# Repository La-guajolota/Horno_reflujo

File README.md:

<!-- @format -->

# 🔥 Homemade SMD Reflow Oven 🔥

## 📑 Table of Contents

- [Overview](#-overview)
- [Project Demo](#-project-demo)
- [Workflow](#-workflow)
- [Technical Challenges](#-technical-challenges)
- [Repository Structure](#-repository-structure)
- [Requirements & Dependencies](#-requirements--dependencies)
- [Installation & Usage](#-installation--usage)
- [To-Do List](#-to-do-list)
- [Possible Improvements](#-possible-improvements)
- [Safety Considerations](#-safety-considerations)
- [Contributing](#-contributing)
- [Reference Links](#-reference-links)
- [License](#-license)

---

## 📝 Overview

The **SMD Reflow Oven** is an open-source project designed for precise SMD soldering. It utilizes configurable thermal profiles managed by an **STM32F411** microcontroller and a web-based GUI hosted on an **ESP01-S**. Key features include real-time PID temperature control, smart power management, and robust safety systems.

> ✅ **Functional Demo**: All core features (PID control, temperature sensing, web GUI, and the reflow algorithm) are fully operational and ready for soldering SMD components.
> 🚧 **Active Development**: Both the firmware and hardware are under continuous improvement.

---

## 📹 Project Demo

See the oven in action! This video demonstrates its current functionality and soldering capabilities.

<p align="center">
<a href="https://youtu.be/XSk6v5LdElc?si=d4BS0npnXu5F3Sj0" target="_blank">
<b>Watch a video demonstration of the oven in action</b>
</a>
</p>

---

## 🔄 Workflow

<details>
<summary><b>Step-by-step SMD soldering process</b></summary>

### 1. 📋 PCB Preparation

- Apply solder paste evenly using a stencil.
- Carefully place the SMD components onto the pasted pads.

### 2. ⚙️ Oven Setup

- Power the oven (120V AC).
- Select the appropriate thermal profile for your solder type via the web GUI.
- Verify that all safety systems are active.

### 3. 🔥 Soldering Process

- Place the prepared PCB inside the oven chamber.
- Close the door securely and start the process from the interface.
- Monitor the temperature curve in real-time to ensure it follows the selected profile.

### 4. 🔍 Final Inspection

- Wait for the **Cooldown** phase to complete before opening the door.
- Allow the PCB to cool completely before handling.
- Inspect the solder joints with a magnifier or microscope for any defects.
- Perform electrical tests to check for shorts or open circuits.

<p align="center">
<a href="https://youtube.com/shorts/ztY0c23UdZQ?si=FxfqCBQ48sNtS6zn" target="_blank">
📺 Watch the final results on YouTube
</a>
</p>
</details>

---

## 🎯 Technical Challenges

| Challenge                 | Solution Approach                                                                                                           |
| :------------------------ | :-------------------------------------------------------------------------------------------------------------------------- |
| **Temperature Control**   | Ensure uniform heat distribution, implement adaptable thermal curves, and design profiles to prevent component microcracks. |
| **Risk Management**       | Implement automatic overheating detection and shutoff, along with a system for filtering potentially toxic vapors.          |
| **Operational Precision** | Calibrate sensors accurately and synchronize heating/cooling stages for reliable and repeatable results.                    |

---

## 📂 Repository Structure

The **Serial Peripheral Interface (SPI)** is crucial in this project for fast communication between the STM32 microcontroller and peripherals like the **MAX6675 thermocouple sensors**, ensuring precise, real-time temperature readings for the PID control loop.

```
.
├── Firmware/                   # Firmware for all microcontrollers
│   ├── esp01/                  # ESP-01S firmware and related tools
│   ├── nextionGUI/             # Nextion HMI screen GUI files
│   └── stm32f411/              # STM32F411 firmware and related tools
├── Hardware/                   # Hardware design files (schematics, PCB)
│   ├── horno_no_modificado/  # Original, unmodified oven schematics
│   └── horno_reflujo/        # Custom reflow oven hardware
├── pictures/                   # Project images and photos
├── .gitignore                  # Git ignore file
├── LICENSE                     # Project license
└── README.md                   # This README file
```

---

## 📦 Requirements & Dependencies

### Software

- **PlatformIO**: Recommended for firmware development.
- **Python 3.x**: For data analysis and utility scripts.
- **KiCad**: For viewing and editing hardware schematics and PCB layouts.
- **STM32CubeIDE**: Optional, for STM32-specific development.

### Hardware

- Refer to the **Bill of Materials (BOM)** located in the `Hardware/horno_reflujo/` directory for a complete list of components.

---

## 🛠️ Installation & Usage

1.  **Clone the Repository:**
    ```bash
    git clone https://github.com/La-guajolota/Horno_reflujo.git
    cd Horno_reflujo
    ```
2.  **Setup Firmware:**
    - Open the `Firmware/` and `stm32f411/` directories in PlatformIO.
    - Follow the specific setup instructions within each folder to compile and upload the firmware.
3.  **Assemble Hardware:**
    - Use the schematics and PCB files in the `Hardware/` directory as a guide.
    - Solder and assemble all components according to the BOM.
4.  **Calibrate & Test:**
    - Before the first use, perform temperature sensor calibration.
    - Test all safety systems to ensure they are functioning correctly.

---

## 📋 To-Do List

### High Priority

- [ ] Complete the documentation for hardware assembly.
- [ ] Implement a physical emergency stop button.
- [ ] Create a detailed guide for sensor calibration procedures.
- [ ] Add unit tests for critical firmware functions.

### Medium Priority

- [ ] Develop a mobile-friendly interface or a dedicated app.
- [ ] Add data logging and analysis features to track performance.
- [ ] Create 3D printable designs for the enclosure.

### Low Priority

- [ ] Integrate with PCB design software for profile suggestions.
- [ ] Add cloud connectivity for remote monitoring.

---

## 🚀 Possible Improvements

### Firmware Enhancements

- **Advanced PID Control**: Implement auto-tuning algorithms and adaptive control for even greater precision.
- **Enhanced Safety**: Add redundant sensors and fail-safe mechanisms.
- **Intuitive UI**: Improve the user interface with a touchscreen, OLED display, or rotary encoder.
- **IoT Integration**: Allow for remote monitoring and control over the internet.
- **Ventilation Control**: Develop an automated system to manage toxic vapor extraction.

### Hardware Upgrades

- **Improved Insulation**: Enhance thermal efficiency and user safety.
- **High-Accuracy Sensors**: Upgrade to more precise temperature sensors.
- **Modular Design**: Create a modular system to support different oven sizes.
- **Power Efficiency**: Optimize heating element control to reduce energy consumption.
- **Electrical Isolation**: Improve electrical isolation between high-voltage and low-voltage circuits.

---

## ⚠️ Safety Considerations

- ⚡ **High Voltage**: This project involves **120V AC**. Exercise extreme caution and ensure all connections are properly insulated.
- 🌡️ **High Temperatures**: The oven reaches temperatures capable of causing severe burns. Use protective equipment.
- 💨 **Ventilation**: Solder paste fumes can be toxic. Operate the oven in a well-ventilated area.
- 🔧 **Grounding**: Ensure the oven chassis is properly grounded to prevent electrical shock.
- 📏 **Calibration**: Regularly calibrate temperature sensors to maintain accuracy and prevent overheating.

---

## 🤝 Contributing

Contributions are welcome\! If you'd like to help improve this project, please follow these steps:

1.  **Fork the repository.**
2.  Create a new branch: `git checkout -b feature/your-amazing-feature`
3.  Make your changes and commit them: `git commit -m 'Add your amazing feature'`
4.  Push to your branch: `git push origin feature/your-amazing-feature`
5.  **Open a Pull Request** and describe the changes you've made.

Please report any bugs or suggest features by opening an issue on GitHub.

---

## 🔗 Reference Links

- [Nextion HMI Displays](https://nextion.tech/) – Official site for Nextion touchscreen displays.
- [gerber_to_scad (GitHub)](https://github.com/kirberich/gerber_to_scad) – Tool for generating 3D stencils from Gerber files.
- [SMD Soldering Guidelines](https://www.surfacemountprocess.com/reflow-soldering-process.html) – Comprehensive guide to the reflow soldering process.
- [Reflow Soldering Profiles (SMTA)](https://www.smta.org/) – Industry resources and recommended thermal profiles.
- [DIY Reflow Oven on Instructables](https://www.instructables.com/DIY-REFLOW-OVEN/) – Step-by-step guide for building a reflow oven with open-source firmware.
- [Hack Your Toaster Oven to Become a Thermocouple Measurement System (All About Circuits)](https://www.allaboutcircuits.com/projects/hack-your-toaster-oven-to-become-a-thermocouple-measurement-system/) – Reference for thermocouple integration and reflow process insights.
- [Better SPI Bus Design in 3 Steps (DorkbotPDX)](https://dorkbotpdx.org/blog/paul/better_spi_bus_design_in_3_steps/) – Key considerations for reliable MAX6675 sensor communication.

---

## 📄 License

This project is licensed under the **MIT License**. See the [LICENSE](https://www.google.com/search?q=LICENSE) file for more details. This means you are free to use, modify, and distribute the project, provided you include the original copyright and license notice.

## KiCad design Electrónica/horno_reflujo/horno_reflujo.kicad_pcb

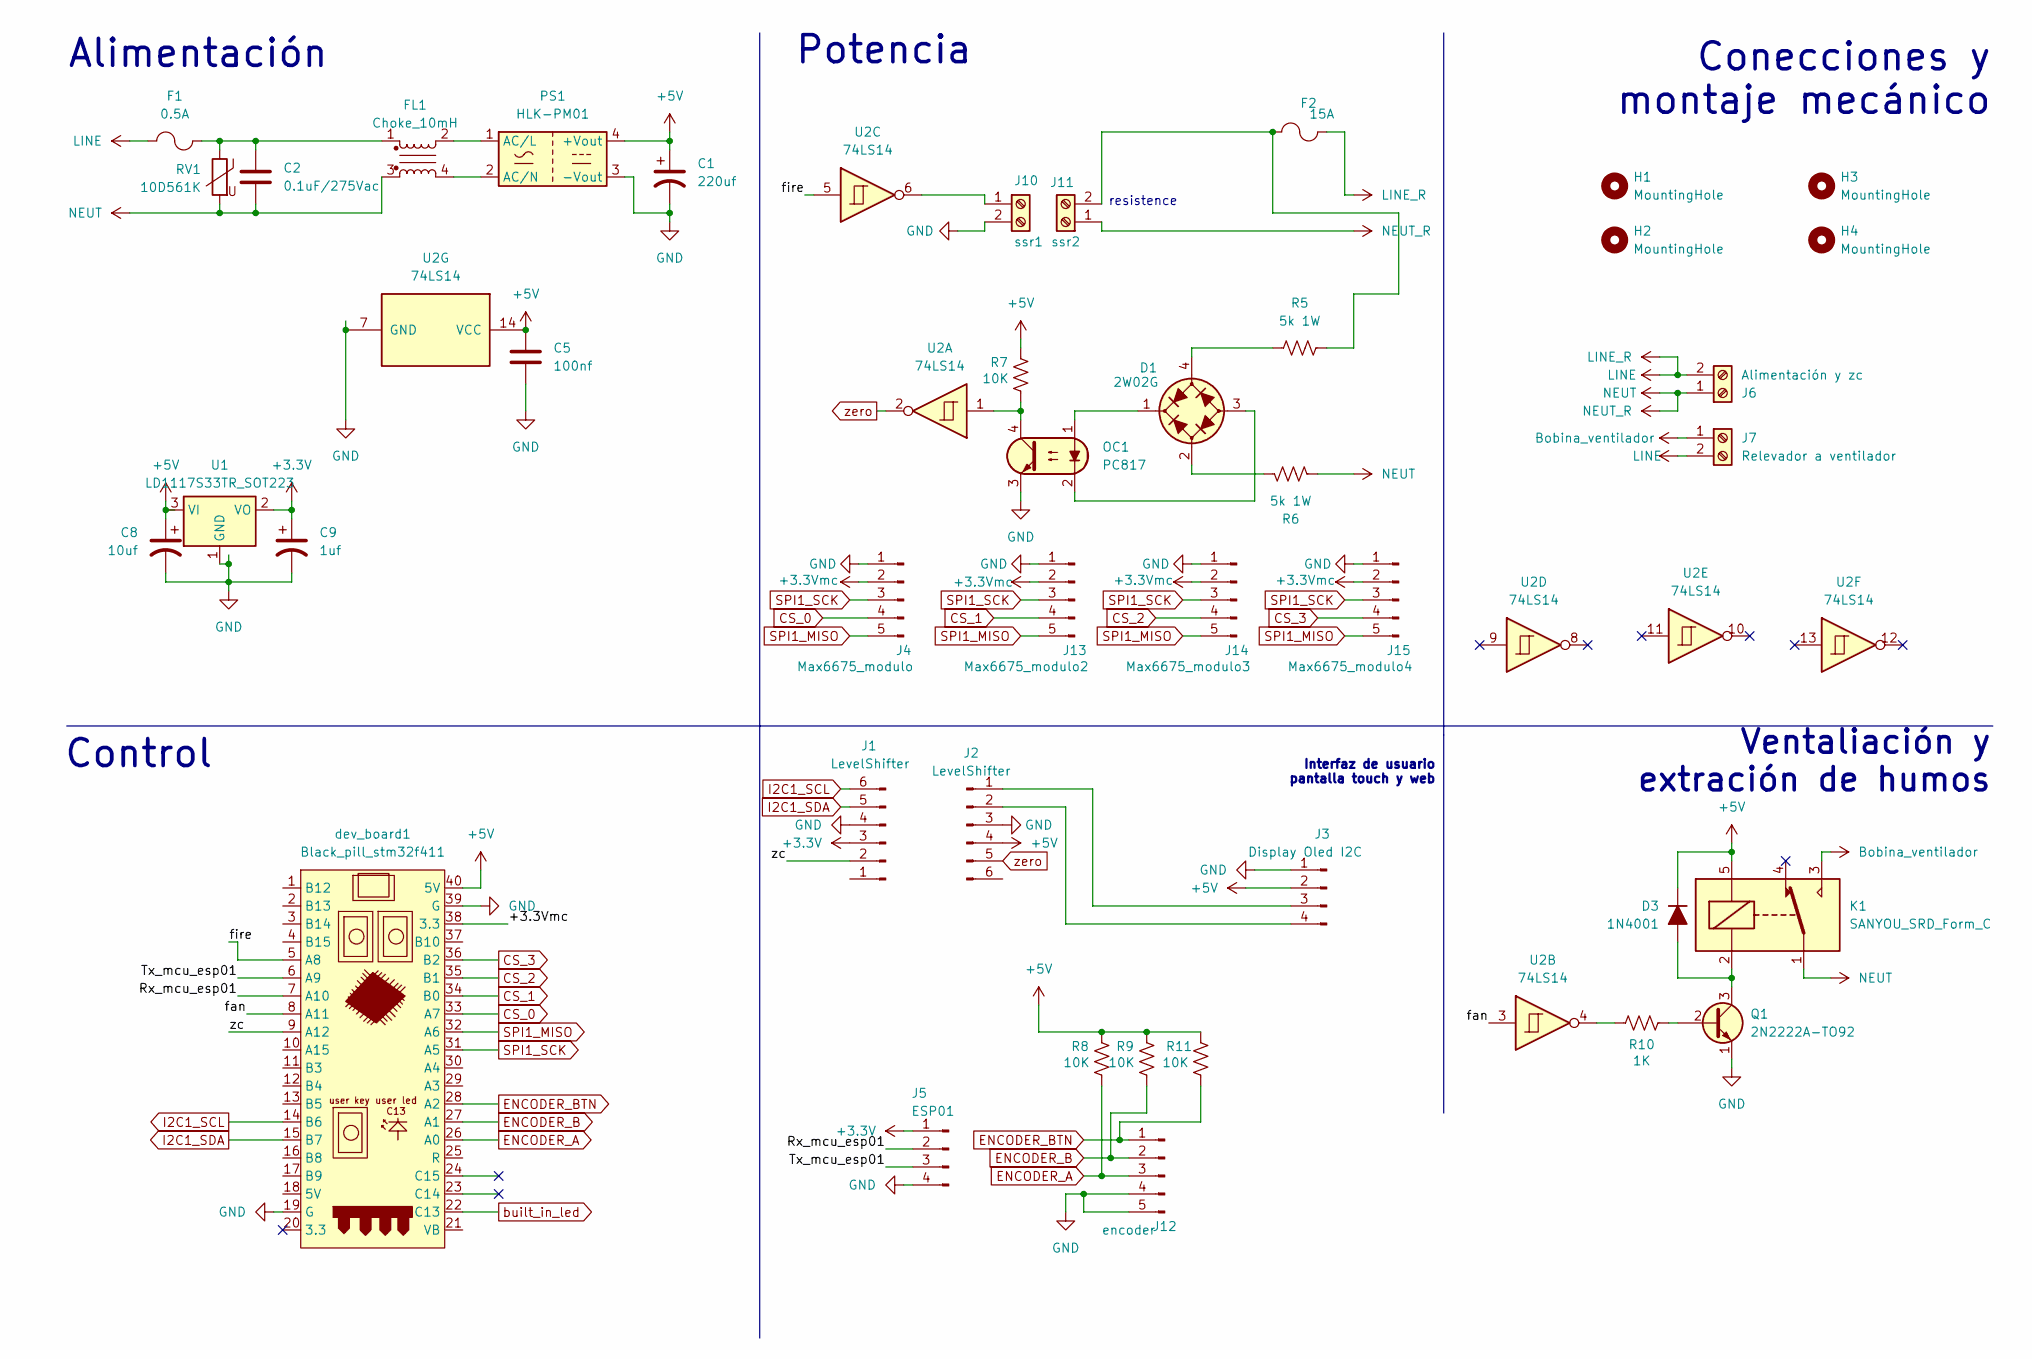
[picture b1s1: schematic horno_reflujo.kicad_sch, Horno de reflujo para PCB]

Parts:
C1: 220uf; CP_Radial_D5.0mm_P2.50mm
C2: 0.1uF/275Vac; C_Disc_D5.1mm_W3.2mm_P5.00mm
C5: 100nf; C_Disc_D5.1mm_W3.2mm_P5.00mm
C8: 10uf; CP_Radial_D5.0mm_P2.50mm
C9: 1uf; CP_Radial_D5.0mm_P2.50mm
D1: 2W02G; Diode_Bridge_Round_D9.0mm
D3: 1N4001; D_A-405_P10.16mm_Horizontal
F1: 0.5A; Fuseholder_Cylinder-5x20mm_Schurter_0031_8201_Horizontal_Op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
F2: 15A; Fuseholder_Cylinder-5x20mm_Schurter_0031_8201_Horizontal_Op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
FL1: Choke_10mH; Choke_Schaffner_RN102-04-14.0x14.0mm
H1, H2, H3, H4: MountingHole; MountingHole_3.2mm_M3_DIN965
J1, J2: LevelShifter; PinHeader_1x06_P2.54mm_Vertical
J3: Display Oled I2C; PinHeader_1x04_P2.54mm_Vertical
J4: Max6675_modulo; PinHeader_1x05_P2.54mm_Vertical
J5: ESP01; PinHeader_1x04_P2.54mm_Vertical
J6: Alimentación y zc; TerminalBlock_bornier-2_P5.08mm
J7: Relevador a ventilador; TerminalBlock_bornier-2_P5.08mm
J10: ssr1; TerminalBlock_bornier-2_P5.08mm
J11: ssr2; TerminalBlock_bornier-2_P5.08mm
J12: encoder; PinHeader_1x05_P2.54mm_Vertical
J13: Max6675_modulo2; PinHeader_1x05_P2.54mm_Vertical
J14: Max6675_modulo3; PinHeader_1x05_P2.54mm_Vertical
J15: Max6675_modulo4; PinHeader_1x05_P2.54mm_Vertical
K1: SANYOU_SRD_Form_C; Relay_SPDT_SANYOU_SRD_Series_Form_C
OC1: PC817; DIP-4_W10.16mm
PS1: HLK-PM01; Converter_ACDC_Hi-Link_HLK-PMxx
Q1: 2N2222A-TO92; TO-92
R5, R6: 5k 1W; R_Axial_DIN0411_L9.9mm_D3.6mm_P5.08mm_Vertical
R7, R8, R9, R11: 10K; R_Axial_DIN0207_L6.3mm_D2.5mm_P2.54mm_Vertical
R10: 1K; R_Axial_DIN0207_L6.3mm_D2.5mm_P2.54mm_Vertical
RV1: 10D561K; RV_Disc_D7mm_W4.2mm_P5mm
U1: LD1117S33TR_SOT223; SOT-223-3_TabPin2
U2: 74LS14; DIP-14_W7.62mm_Socket_LongPads
dev_board1: Black_pill_stm32f411; Maple_Mini

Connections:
+3.3V: C9.1, J1.3, J5.1, U1.2 (VO)
+3.3Vmc: J4.2, J13.2, J14.2, J15.2, dev_board1.38 (3.3)
+5V: C1.1, C5.1, C8.1, D3.1 (K), J2.4, J3.2, K1.5, PS1.4 (+Vout), R7.2, R8.2, R9.2, R11.2, U1.3 (VI), U2.14 (VCC), dev_board1.40 (5V)
/Rx_mcu_esp01: J5.2, dev_board1.7 (A10)
/Tx_mcu_esp01: J5.3, dev_board1.6 (A9)
/fan: U2.3, dev_board1.8 (A11)
/fire: U2.5, dev_board1.5 (A8)
/zc: J1.2, dev_board1.9 (A12)
Bobina_ventilador: J7.1, K1.3
CS_0: J4.4, dev_board1.33 (A7)
CS_1: J13.4, dev_board1.34 (B0)
CS_2: J14.4, dev_board1.35 (B1)
CS_3: J15.4, dev_board1.36 (B2)
ENCODER_A: J12.3, R8.1, dev_board1.26 (A0)
ENCODER_B: J12.2, R9.1, dev_board1.27 (A1)
ENCODER_BTN: J12.1, R11.1, dev_board1.28 (A2)
GND: C1.2, C5.2, C8.2, C9.2, J1.4, J2.3, J3.1, J4.1, J5.4, J10.2, J12.4, J12.5, J13.1, J14.1, J15.1, OC1.3, PS1.3 (-Vout), Q1.1 (E), U1.1 (GND), U2.7 (GND), dev_board1.19 (G), dev_board1.39 (G)
I2C1_SCL: J1.6, dev_board1.14 (B6)
I2C1_SDA: J1.5, dev_board1.15 (B7)
LINE: F1.1, F2.1, J6.2, J7.2
NEUT: C2.2, FL1.3, J6.1, J11.1, K1.1, R6.2, RV1.2
unnamed: C2.1, F1.2, FL1.1, RV1.1
unnamed: D1.2 (1), R6.1
unnamed: D1.4 (2), R5.1
unnamed: D1.1 (+), OC1.1
unnamed: D1.3 (-), OC1.2
unnamed: D3.2 (A), K1.2, Q1.3 (C)
unnamed: J2.1, J3.3
unnamed: J2.2, J3.4
unnamed: J10.1, U2.6
unnamed: F2.2, J11.2, R5.2
unnamed: OC1.4, R7.1, U2.1
unnamed: FL1.2, PS1.1 (AC/L)
unnamed: FL1.4, PS1.2 (AC/N)
unnamed: Q1.2 (B), R10.1
unnamed: R10.2, U2.4
SPI1_MISO: J4.5, J13.5, J14.5, J15.5, dev_board1.32 (A6)
SPI1_SCK: J4.3, J13.3, J14.3, J15.3, dev_board1.31 (A5)
built_in_led: dev_board1.22 (C13)
zero: J2.5, U2.2

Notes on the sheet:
Alimentación
Interfaz de usuario pantalla touch y web
Ventaliación y extración de humos
resistence
Conecciones y montaje mecánico
Potencia
Control

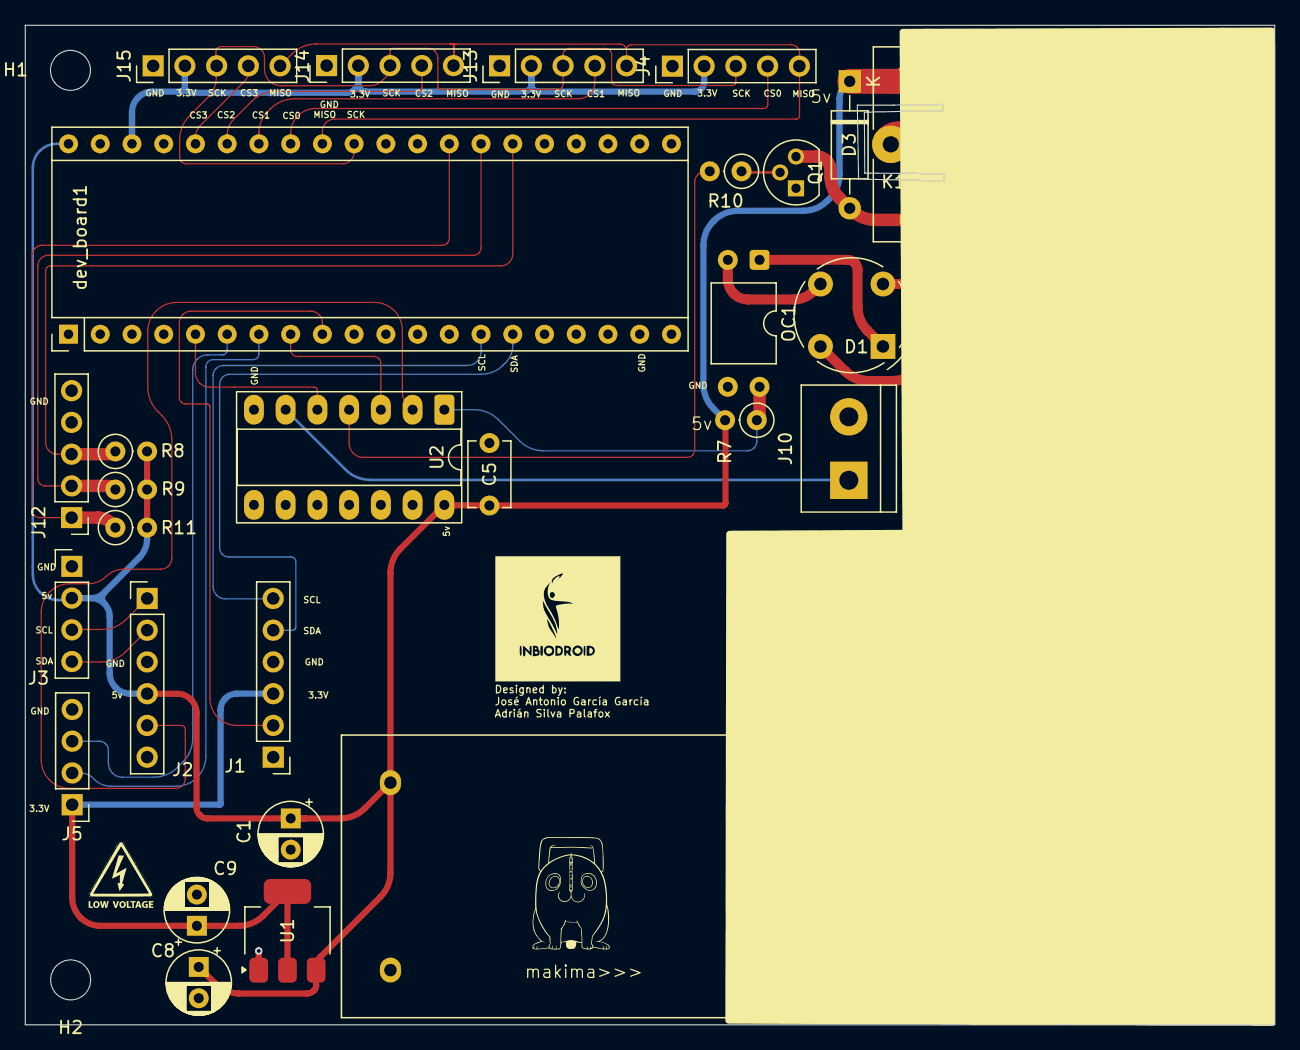
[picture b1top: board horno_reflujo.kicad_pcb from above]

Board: 2 copper layers, 100.0 x 80.0 mm, 42 parts (0 on the bottom side), 39 nets.

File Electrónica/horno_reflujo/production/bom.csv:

Designator,Footprint,Quantity,Value,LCSC Part #
C1,CP_Radial_D5.0mm_P2.50mm,1,220uf,
C2,C_Disc_D5.1mm_W3.2mm_P5.00mm,1,0.1uF/275Vac,
C5,C_Disc_D5.1mm_W3.2mm_P5.00mm,1,100nf,
C8,CP_Radial_D5.0mm_P2.50mm,1,10uf,
C9,CP_Radial_D5.0mm_P2.50mm,1,1uf,
D1,Diode_Bridge_Round_D9.0mm,1,2W02G,
D3,D_A-405_P10.16mm_Horizontal,1,1N4001,
DEV_BOARD1,Maple_Mini,1,Black_pill_stm32f411,
F1,Fuseholder_Cylinder-5x20mm_Schurter_0031_8201_Horizontal_Open,1,0.5A,
F2,Fuseholder_Cylinder-5x20mm_Schurter_0031_8201_Horizontal_Open,1,15A,
FL1,Choke_Schaffner_RN102-04-14.0x14.0mm,1,Choke_10mH,
"J1, J2",PinHeader_1x06_P2.54mm_Vertical,2,LevelShifter,
J10,TerminalBlock_bornier-2_P5.08mm,1,ssr1,
J11,TerminalBlock_bornier-2_P5.08mm,1,ssr2,
J12,PinHeader_1x05_P2.54mm_Vertical,1,encoder,
J13,PinHeader_1x05_P2.54mm_Vertical,1,Max6675_modulo2,
J14,PinHeader_1x05_P2.54mm_Vertical,1,Max6675_modulo3,
J15,PinHeader_1x05_P2.54mm_Vertical,1,Max6675_modulo4,
J3,PinHeader_1x04_P2.54mm_Vertical,1,Display Oled I2C,
J4,PinHeader_1x05_P2.54mm_Vertical,1,Max6675_modulo,
J5,PinHeader_1x04_P2.54mm_Vertical,1,ESP01,
J6,TerminalBlock_bornier-2_P5.08mm,1,Alimentación y zc,
J7,TerminalBlock_bornier-2_P5.08mm,1,Relevador a ventilador,
K1,Relay_SPDT_SANYOU_SRD_Series_Form_C,1,SANYOU_SRD_Form_C,
OC1,DIP-4_W10.16mm,1,PC817,
PS1,Converter_ACDC_Hi-Link_HLK-PMxx,1,HLK-PM01,
Q1,TO-92,1,2N2222A-TO92,
R10,R_Axial_DIN0207_L6.3mm_D2.5mm_P2.54mm_Vertical,1,1K,
"R11, R7, R8, R9",R_Axial_DIN0207_L6.3mm_D2.5mm_P2.54mm_Vertical,4,10K,
"R5, R6",R_Axial_DIN0411_L9.9mm_D3.6mm_P5.08mm_Vertical,2,5k  1W,
RV1,RV_Disc_D7mm_W4.2mm_P5mm,1,10D561K,
U1,SOT-223-3_TabPin2,1,LD1117S33TR_SOT223,
U2,DIP-14_W7.62mm_Socket_LongPads,1,74LS14,

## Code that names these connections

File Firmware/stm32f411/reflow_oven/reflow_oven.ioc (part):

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Mcu.Name=STM32F411C(C-E)Ux
Mcu.Package=UFQFPN48
Mcu.UserName=STM32F411CEUx
PA0-WKUP.GPIOParameters=GPIO_Label
PA0-WKUP.GPIO_Label=encoder_A
PA0-WKUP.Signal=S_TIM2_CH1_ETR
PA1.GPIOParameters=GPIO_Label
PA1.GPIO_Label=encoder_B
PA1.Signal=S_TIM2_CH2
PA10.Mode=Asynchronous
PA10.Signal=USART1_RX
PA11.GPIOParameters=PinState,GPIO_PuPd,GPIO_Label,GPIO_ModeDefaultOutputPP
PA11.GPIO_Label=fan_relay
PA11.GPIO_ModeDefaultOutputPP=GPIO_MODE_OUTPUT_PP
PA11.GPIO_PuPd=GPIO_PULLUP
PA11.PinState=GPIO_PIN_SET
PA11.Signal=GPIO_Output
PA12.GPIOParameters=GPIO_Label
PA12.GPIO_Label=zc_crossing
PA12.Signal=S_TIM1_ETR
PA13.Mode=Serial_Wire
PA13.Signal=SYS_JTMS-SWDIO
PA14.Mode=Serial_Wire
PA14.Signal=SYS_JTCK-SWCLK
PA2.GPIOParameters=GPIO_PuPd,GPIO_Label,GPIO_ModeDefaultEXTI
PA2.GPIO_Label=encoder_pulse
PA2.GPIO_ModeDefaultEXTI=GPIO_MODE_IT_FALLING
PA2.GPIO_PuPd=GPIO_PULLUP
PA2.Signal=GPXTI2
PA5.Mode=RX_Only_Simplex_Unidirect_Master
PA5.Signal=SPI1_SCK
PA6.Mode=RX_Only_Simplex_Unidirect_Master
PA6.Signal=SPI1_MISO
PA7.GPIOParameters=GPIO_Speed,PinState,GPIO_PuPd,GPIO_Label
PA7.GPIO_Label=CS_0
PA7.GPIO_PuPd=GPIO_PULLUP
PA7.GPIO_Speed=GPIO_SPEED_FREQ_HIGH
PA7.PinState=GPIO_PIN_SET
PA7.Signal=GPIO_Output
PA8.GPIOParameters=GPIO_ModeDefaultPP,GPIO_Speed,GPIO_PuPd,GPIO_Label
PA8.GPIO_Label=fire
PA8.GPIO_ModeDefaultPP=GPIO_MODE_AF_PP
PA8.GPIO_PuPd=GPIO_PULLUP
PA8.GPIO_Speed=GPIO_SPEED_FREQ_VERY_HIGH
PA8.Signal=S_TIM1_CH1
PA9.Mode=Asynchronous
PA9.Signal=USART1_TX
PB0.GPIOParameters=GPIO_Speed,GPIO_PuPd,GPIO_Label
PB0.GPIO_Label=CS_3
PB0.GPIO_PuPd=GPIO_PULLUP
PB0.GPIO_Speed=GPIO_SPEED_FREQ_HIGH
PB0.Signal=GPIO_Output
PB1.GPIOParameters=GPIO_Speed,GPIO_PuPd,GPIO_Label
PB1.GPIO_Label=CS_2
PB1.GPIO_PuPd=GPIO_PULLUP
PB1.GPIO_Speed=GPIO_SPEED_FREQ_HIGH
PB1.Signal=GPIO_Output
PB2.GPIOParameters=GPIO_Speed,PinState,GPIO_PuPd,GPIO_Label
PB2.GPIO_Label=CS_1
PB2.GPIO_PuPd=GPIO_PULLUP
PB2.GPIO_Speed=GPIO_SPEED_FREQ_HIGH
PB2.PinState=GPIO_PIN_SET
PB2.Signal=GPIO_Output
PB6.Mode=I2C
PB6.Signal=I2C1_SCL
PB7.Mode=I2C
PB7.Signal=I2C1_SDA
PC13-ANTI_TAMP.GPIOParameters=GPIO_Label
PC13-ANTI_TAMP.GPIO_Label=built_in_led
PC13-ANTI_TAMP.Signal=GPIO_Output
PC14-OSC32_IN.Mode=LSE-External-Oscillator
PC14-OSC32_IN.Signal=RCC_OSC32_IN
PC15-OSC32_OUT.Mode=LSE-External-Oscillator
PC15-OSC32_OUT.Signal=RCC_OSC32_OUT
PH0\ -\ OSC_IN.Mode=HSE-External-Oscillator
PH0\ -\ OSC_IN.Signal=RCC_OSC_IN
PH1\ -\ OSC_OUT.Mode=HSE-External-Oscillator
PH1\ -\ OSC_OUT.Signal=RCC_OSC_OUT
RCC.HSE_VALUE=25000000
RCC.SYSCLKFreq_VALUE=100000000
RCC.SYSCLKSource=RCC_SYSCLKSOURCE_PLLCLK
board=custom

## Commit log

2025-03-10 test0
2025-03-10 update del readme
2025-03-10 Agregada la licencia MIT
2025-03-10 corrección licencia MIT
2025-03-11 Limpiando rama y dejando solo los archivos necesarios
2025-03-11 Link google sheets y readme de Presupuestos/
2025-03-11 modified: Presupuestos_materiales/README.md
2025-03-27 new file: "Electr\303\263nica/horno_no_modificado/esquema_horno_no_modificado-backups/esquema_horno_no_modificado-2025-03-23_174911.zip" new file: "Electr\303\263nica/horno_no_modificado/esquema_horn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
2025-03-30 new file: "Electr\303\263nica/horno_reflujo/horno_reflujo-backups/horno_reflujo-2025-03-27_104626.zip" new file: Firmware/nextionGUI/fuentes/text0.zi new file: Firmware/nextionGUI/guiproject4832.HMI 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
2025-03-30 Agregada carpeta Firmware desde main
2025-03-31 Diseño de GUI para el horno, firmware de la pantalla
2025-03-31 deleted: "Investigaci\303\263n_fuentes/notas_d_aplicacion/AN-3004JP.pdf" deleted: "Investigaci\303\263n_fuentes/notas_d_aplicacion/zero_crossing.pdf" deleted: Presupuestos_materiales/README.md delete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
2025-03-31 new file: README.md SE BORRÓ POR ACCIDENTE
2025-03-31 deleted: Firmware/nextionGUI/guiproject4832.HMI
2025-03-31 new file: .gitignore
2025-03-31 new file: LICENSE
2025-04-04 stm32 reflow_oven proyecto
2025-04-04 deleted: Presupuestos_materiales/compras/.~lock.Cotizacion_mercadolibre.xlsx# deleted: Presupuestos_materiales/compras/.~lock.cotizacion_welectronics.xlsx# deleted: Presupuestos_materiales/compras/Co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
2025-04-23 Estado limpio del proyecto
2025-04-23 modified: .gitignore
2025-04-24 max6675_libray PID_library
2025-04-25 modified: Firmware/reflow_oven/.settings/language.settings.xml modified: Firmware/reflow_oven/Core/Inc/gui_backend.h modified: Firmware/reflow_oven/Core/Inc/main.h modified: Firmware/reflow_oven/Core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
2025-04-25 timersconfig reflowoven_logic
2025-04-25 modified: Firmware/reflow_oven/Core/Src/reflow_oven_process.c
2025-04-25 timersconfig reflowoven_logic2
2025-04-25 README updated
2025-04-25 readme added
2025-04-25 Liscencia agregada
2025-05-15 GUI eezstudio
2025-05-16 first update pcb
2025-05-16 pcb updated :)
2025-05-16 LVGL and EEZstudio imports
2025-05-16 third_parties added | reorganization of folders
2025-05-16 screen lib add to stm32f4 code
2025-05-27 redesigned pcb
2025-05-30 final check
2025-05-30 reorganizacion de folders
2025-05-30 actualización del main
2025-05-31 Added creators' names to PCB desig
2025-05-31 actualizacion al main
2025-05-31 adrian revision pcb
2025-05-31 copia de main a rama
2025-05-31 adrian revision pcb2
2025-05-31 copia de main
2025-05-31 copia de carpeta electrónica
2025-06-01 mounting holes update
2025-06-01 mcu pin update
2025-06-01 lvgl test
2025-06-01 trash files deleted
2025-06-02 full integration of lvgl to proyect| todo: modify screendriver
2025-06-02 actualizacion de placa
2025-06-02 Update pcb
2025-06-13 review
2025-07-07 esp01 GUI integration
2025-07-08 74ls04 inputs are now grounded
2025-07-08 74ls04 inputs now have pull-up/down resistors
2025-07-09 Creation of ESP01_gui and refactory of STM32F411
2025-07-09 DMA TX from STM32 to ESP01 and refactory
2025-07-10 DMA RX from STM32 start
2025-07-15 DMA RX-TX fully added
2025-07-15 doxeada
2025-07-19 esp01 web server firmware
2025-07-20 Firmware debug
2025-07-21 Firmware debug 2
2025-07-22 Firmware debug 3
2025-07-22 Firmware refactory
2025-07-23 Firmware refactory2
2025-07-26 Firmware refactory3
2025-07-27 Firmware Debug4
2025-07-28 DMA reset handle due to esp01 boot message addded
2025-07-28 refactory 5
2025-08-07 EMA filter added and sampling modified to 4HZ
2025-08-12 DEBUG_MODES added and PID gains tunned
2025-08-12 OCTAVE code for regresions in plant
2025-08-28 web_client script was refacterd to be more secure and also updated the themocuples responses to STEP
2025-09-11 Functional Demo
2025-09-11 Documentation v1 functional demo
2025-09-11 Documentation v1 functional demo (esp01)
2025-09-11 Documentation v1 functional demo (stm32f411)
2025-09-11 Documentation v1 functional demo (Firmware)
2025-09-11 Documentation v1 functional demo (Hardware)
2025-10-23 documentation updated
